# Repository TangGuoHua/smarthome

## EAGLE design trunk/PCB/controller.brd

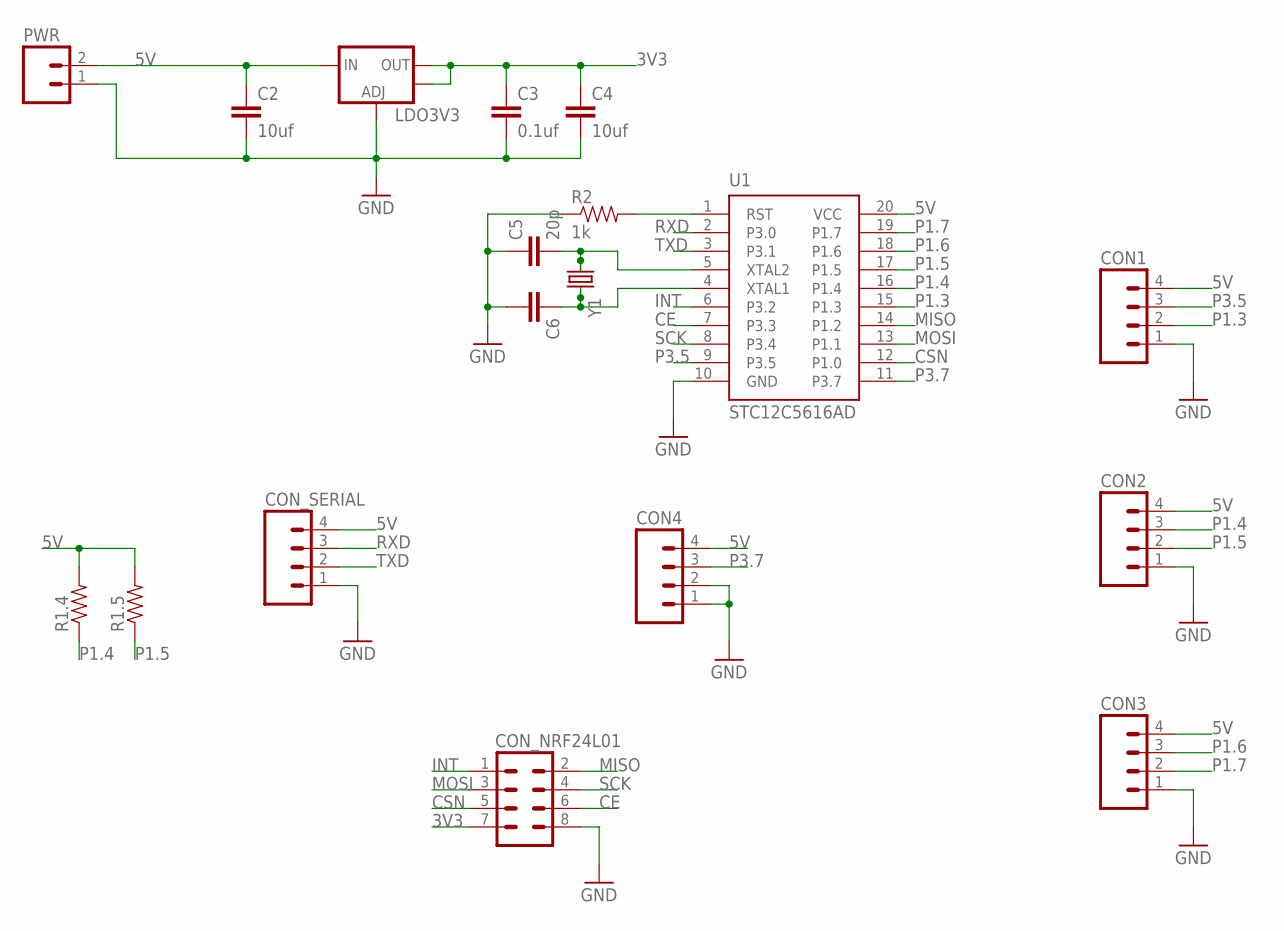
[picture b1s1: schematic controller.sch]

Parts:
C2, C4: 10uf; 0805
C3: 0.1uf; 0805
C5: 20p; 0603-CAP
C6: CAP0603-CAP; 0603-CAP
CON1, CON2, CON3, CON4: M04PTH; 1X04
CON_NRF24L01: M04X2; 2X4
CON_SERIAL: M04PTH; 1X04
LDO3V3: V_REG_LM1117SOT223; SOT223
PWR: M02PTH; 1X02
R1.4, R1.5: RESISTOR0805-RES; 0805
R2: 1k; 0805
U1: STC12C5616AD; SOP20
Y1: CRYSTALHC49US; HC49US

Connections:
3V3: C3.1, C4.1, CON_NRF24L01.7, LDO3V3.2 (OUT), LDO3V3.4 (OUT)
5V: C2.1, CON1.4, CON2.4, CON3.4, CON4.4, CON_SERIAL.4, LDO3V3.3 (IN), PWR.2, R1.4.2, R1.5.2, U1.20 (VCC)
CE: CON_NRF24L01.6, U1.7 (P3.3)
CSN: CON_NRF24L01.5, U1.12 (P1.0)
GND: C2.2, C3.2, C4.2, C5.1, C6.2, CON1.1, CON2.1, CON3.1, CON4.1, CON4.2, CON_NRF24L01.8, CON_SERIAL.1, LDO3V3.1 (ADJ), PWR.1, R2.1, U1.10 (GND)
INT: CON_NRF24L01.1, U1.6 (P3.2)
MISO: CON_NRF24L01.2, U1.14 (P1.2)
MOSI: CON_NRF24L01.3, U1.13 (P1.1)
unnamed: C5.2, U1.5 (XTAL2), Y1.1
unnamed: C6.1, U1.4 (XTAL1), Y1.2
unnamed: R2.2, U1.1 (RST)
P1.3: CON1.2, U1.15 (P1.3)
P1.4: CON2.3, R1.4.1, U1.16 (P1.4)
P1.5: CON2.2, R1.5.1, U1.17 (P1.5)
P1.6: CON3.3, U1.18 (P1.6)
P1.7: CON3.2, U1.19 (P1.7)
P3.5: CON1.3, U1.9 (P3.5)
P3.7: CON4.3, U1.11 (P3.7)
RXD: CON_SERIAL.3, U1.2 (P3.0)
SCK: CON_NRF24L01.4, U1.8 (P3.4)
TXD: CON_SERIAL.2, U1.3 (P3.1)

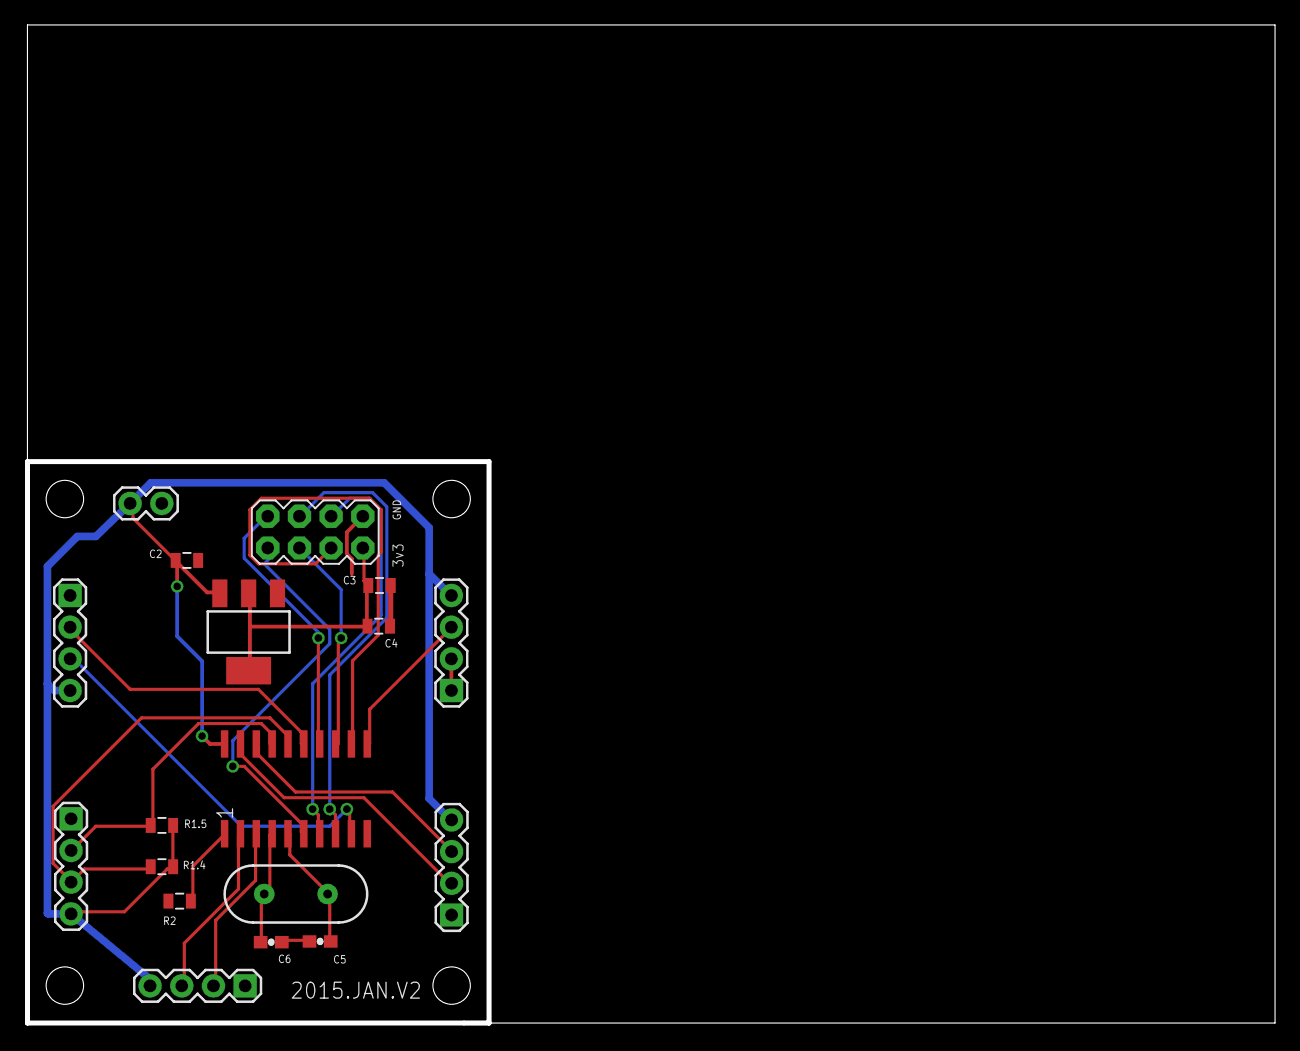
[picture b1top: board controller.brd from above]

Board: 2 copper layers, 99.8 x 79.8 mm, 18 parts (0 on the bottom side), 21 nets.

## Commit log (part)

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2014-08-24 增加rfPower maxRetry参数
2014-09-05 增加52#节点，客厅吊顶射灯控制器
2014-09-14 2014-SEP-14 黄长浩 客厅吊顶射灯实现“全开全关”
2014-09-14 恢复10分钟采样
2014-09-15 backup db
2014-09-23 修改nrf24l01+驱动，以使得带PA的模块可以收到Ack 增加tabDataSent 修改log.php样式
2014-09-27 重新设计tabDataToNode表 nrf24l01+驱动修改，以支持3－5字节的收发地址
2014-09-27 智能家2代上线
2014-09-28 一代主机的最终数据备份
2014-09-28 adding script to update external ip
2014-09-29 restructure folder
2014-10-02 升级厨房灯控节点22，增加回传数据
2014-10-03 2014年10月03日 黄长浩 增加小厨宝自动工作模式 增加EEPROM保存数据 向Pi发送数据的延时由原10s延时计数改为timer0中断计数
2014-10-04 升级51号节点
2014-10-04 2014-OCT-04 黄长浩 电视背景墙控制器增加电视、电信机顶盒的控制 调整显示顺序按DisplayOrder排
2014-10-05 2014-OCT-05 黄长浩 tabDataSent表增加fldRequestor字段
2014-10-05 rename folders
2014-10-06 2014年10月06日 黄长浩 修改initDelay()延时为(NodeID*2)秒
2014-10-13 2014-OCT-05 黄长浩 增加execSql()方法，整理main()函数的主While循环结构
2014-10-15 2014年10月15日 黄长浩 nrfDataAvailable()取代nrfIsDataReceived() nrfGetOneDataPacket()取代nrfGetReceivedData() 支持从缓存FIFO读取多字节数据
2014-10-16 UTF8 without BOM
2014-10-19 2014-OCT-19 黄长浩 增加室外温度亮度（阳台）
2014-11-30 2014-NOV-30 黄长浩 增加客厅取暖器及温控
2014-11-30 2014年10月12日 黄长浩 增加取暖器温控
2014-11-30 增加功能号9－错误异常报告
2014-12-07 增加特定事件报告
2014-12-28 tmp save
2015-02-01 书房灯带节点升级

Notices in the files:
parts and their libraries:
SparkFun-Capacitors: Licensing: Creative Commons ShareAlike 4.0 International - https://creativecommons.org/licenses/by-sa/4.0
